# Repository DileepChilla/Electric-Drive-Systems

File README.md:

# 24 V / 250 W Brushed DC Motor Driver

**IR2104 half-bridge · 2× IRFZ44N · ATmega328P closed-loop control**

Design, simulation, PCB layout, firmware and bench validation of a complete motor
drive for a MY1016 24 V 250 W brushed DC motor. Built for ELT10140 *Electric Drive
Systems*, Westsächsische Hochschule Zwickau, summer semester 2026.

---

## What this is

A single-quadrant (unidirectional) drive with hardware and software overcurrent
protection, soft-start, stall detection and a five-state supervisory state machine.
The design was carried through the full V-cycle: analytical sizing → SPICE/VSM
co-simulation → averaged-model verification in Simulink → PCB layout → assembly →
bench test.

| Metric | Value |
|---|---|
| Supply | 24 V DC, 15 A fused |
| Rated output | 250 W |
| Switching frequency | 20 kHz (Timer1 Fast PWM, ICR1 top) |
| Duty resolution | 10 bit (ICR1 = 799 @ 16 MHz, /1 prescaler) |
| Current sense | 10 mΩ shunt, ×16 non-inverting, 0–31 A → 0–5 V |
| Overcurrent trip | Hardware SD assert + firmware stall detect (> 20 A for > 1 s) |
| Board | 2-layer FR-4, 1.55 mm, 35 µm Cu |

---

## Architecture

```
24 V ──┬── LM2596 buck ──── 5 V ──── ATmega328P (Arduino Nano)
       │                                  │ OC1A (D9) ──► IN
       ├── L7812CV linear ── 12 V ────► IR2104 ──┬──► HO ──► Q1 (IRFZ44N, high side)
       │                                  ▲      └──► LO ──► Q2 (IRFZ44N, low side)
       │                            SD ───┘
       │                          (D8 + hardware fault)
       │
       └── power rail ──► Q1 drain
                          switch node ──► MY1016 motor ──► MBR2045CT ──► shunt ──► GND
                                                                          │
                                                          LM358 ×16 ──► ADC0 (A0)
```

### Design decisions worth defending

**IR2104 VCC must be 12 V, not 24 V and not 5 V.**
The device UVLO sits at ~8.2 V rising, so 5 V logic rails cannot drive it; 24 V exceeds
its absolute maximum. A dedicated L7812CV linear regulator supplies VCC. This is the
single most common way to destroy an IR2104 and the reason the design carries a second
regulator despite the buck already producing 5 V.

**Bootstrap sizing.**
1 µF ceramic + 1N4148 fast diode. At 20 kHz the high-side gate charge (Q_g ≈ 63 nC for
IRFZ44N) is replenished every 50 µs; the capacitor must hold V_BS above the 8.0 V
bootstrap UVLO across the maximum on-time. Minimum duty is clamped in firmware so the
low-side device always conducts long enough to recharge.

**Synchronous rectification over a plain flyback diode.**
Q2's channel resistance (17.5 mΩ) dissipates less than the forward drop of the Schottky
during freewheeling. The MBR2045CT remains as a parallel path covering the dead time
and as a fail-safe if the low-side gate drive is lost.

**20 kHz PWM.**
Above the audible band, below the point where IRFZ44N switching losses become the
dominant thermal term (≈ 0.35 W per device at rated current with 10 Ω gate resistors).

**Two independent overcurrent layers.**
Hardware pulls SD low in sub-microsecond time — fast enough for a short circuit.
Firmware stall detection acts on the filtered ADC current over a 1 s window — slow, but
it distinguishes a genuine mechanical jam from inrush. Neither alone is sufficient.

---

## Repository layout

```
├── firmware/          Arduino/AVR source — PWM, ADC, state machine, protection
├── hardware/
│   ├── kicad/         KiCad 10 project: schematic, PCB, footprints
│   ├── gerbers/       Fabrication output + drill files
│   └── datasheets/    Component datasheets referenced in the design
├── simulation/
│   ├── proteus/       Proteus VSM mixed-signal co-simulation (.pdsprj)
│   ├── simulink/      Averaged-model plant + discrete state machine (.slx)
│   └── results/       Captured waveforms, step responses, fault traces
├── design/            Engineering notes and derivations
├── report/            Final report (PDF) and presentation
├── bom/               Bill of materials (CSV + PDF)
└── images/            Diagrams, board photos, schematic exports
```

---

## Firmware

Bare-register AVR C++, no Arduino `analogWrite`. Timer1 in Fast PWM mode 14
(TOP = ICR1) gives a fixed 20 kHz carrier with 10-bit duty resolution.

State machine:

```
OFF ──start──► STARTING ──ramp complete──► RUNNING
 ▲                 │                          │
 │                 └──────overcurrent─────────┤
 │                                            │
 └── BRAKING ◄── stop ──────────────────────► FAULT
```

- `STARTING` ramps duty linearly to limit inrush through the motor's armature inductance.
- `FAULT` latches: SD is driven low and the state persists until an explicit reset.
- `BRAKING` shorts the armature through Q2 for dynamic braking.
- Current is read in a 4-sample exponential moving average to reject switching noise
  without adding the phase lag of a long boxcar filter.

Build: Arduino IDE or PlatformIO, target `nanoatmega328new`, 16 MHz.

---

## Simulation

**Proteus VSM** — the only tool in the chain that runs the compiled firmware against a
SPICE model of the analog stage simultaneously. Used to verify gate drive timing,
bootstrap charging, and that the ADC path actually produces the expected count for a
known shunt current.

> Note: Proteus *Analogue Analysis* is pure SPICE and does not execute the MCU
> firmware. Mixed-signal capture requires the VSM Oscilloscope instrument.
> AREF (ATmega328P pin 20) must be tied to +5 V or every ADC read returns zero and the
> overcurrent path silently fails.

**Simulink** — `MotorDriverAveraged.slx` replaces the switching stage with a duty-cycle
averaged model, letting the electrical (R–L–back-EMF) and mechanical (J–B–T_load)
dynamics run at reasonable step sizes. The firmware state machine is reimplemented in a
discrete MATLAB Function block, together with 10-bit ADC quantisation and the LM358
scaling, so the simulated controller sees the same numbers the real one does.

Two validated scenarios: light-load run-and-brake, and a rotor jam triggering the fault
path.

*Known limitation:* the load-torque model is constant rather than velocity-dependent, so
after a fault the plant shows a small reverse rotation that the real machine does not.
Documented rather than hidden — fixing it requires a Coulomb-friction/zero-speed
constraint on the mechanical block.

---

## Bill of materials

Full BOM in `bom/`. Principal parts:

| Ref | Part | Function |
|---|---|---|
| M1 | MY1016 | 24 V 250 W brushed DC motor |
| U1 | IR2104 | Half-bridge gate driver, bootstrap high-side |
| Q1, Q2 | IRFZ44N | 55 V / 49 A N-channel MOSFET, R_DS(on) 17.5 mΩ |
| D2 | MBR2045CT | 20 A Schottky freewheeling diode |
| U2 | LM358 | Current-sense amplifier, gain 16 |
| U4 | LM2596 module | 24 V → 5 V switching regulator |
| U5 | L7812CV | 24 V → 12 V linear regulator (IR2104 VCC) |
| D1 | 1N4148 | Bootstrap diode |
| — | SMBJ33A | Transient voltage suppressor, input protection |
| R_sh | 10 mΩ, 3 W | Current-sense shunt |

Mechanical: 400 × 300 × 12 mm birch plywood mounting board, ferrule-crimped
connections throughout.

---

## Reproducing

1. Open `hardware/kicad/` in KiCad 10.0 or later.
2. Flash `firmware/` to an Arduino Nano (ATmega328P, 16 MHz).
3. Supply 24 V through a 15 A fuse. **Confirm the L7812CV output is 12 V before
   connecting IR2104 VCC.**
4. Verify the switch node with an isolated probe before attaching the motor.

---

## Course context

ELT10140 Electric Drive Systems, SoSe 2026 · Westsächsische Hochschule Zwickau
Supervisors: Prof. Dr.-Ing. J. Zitzelsberger, Prof. U. David, Prof. R. Lehmann
Team 1 — Leo Kämpf (team lead), Dileep Chilla (documentation, simulation, PCB),
Vaibhav, Rahul, Shashank, Usman, Vaishali, Laert

Course handouts and lecture material are the property of WHZ and are not redistributed
in this repository.

## Licence

Source code and design files: MIT (see `LICENSE`).
Documentation and figures: CC BY 4.0.

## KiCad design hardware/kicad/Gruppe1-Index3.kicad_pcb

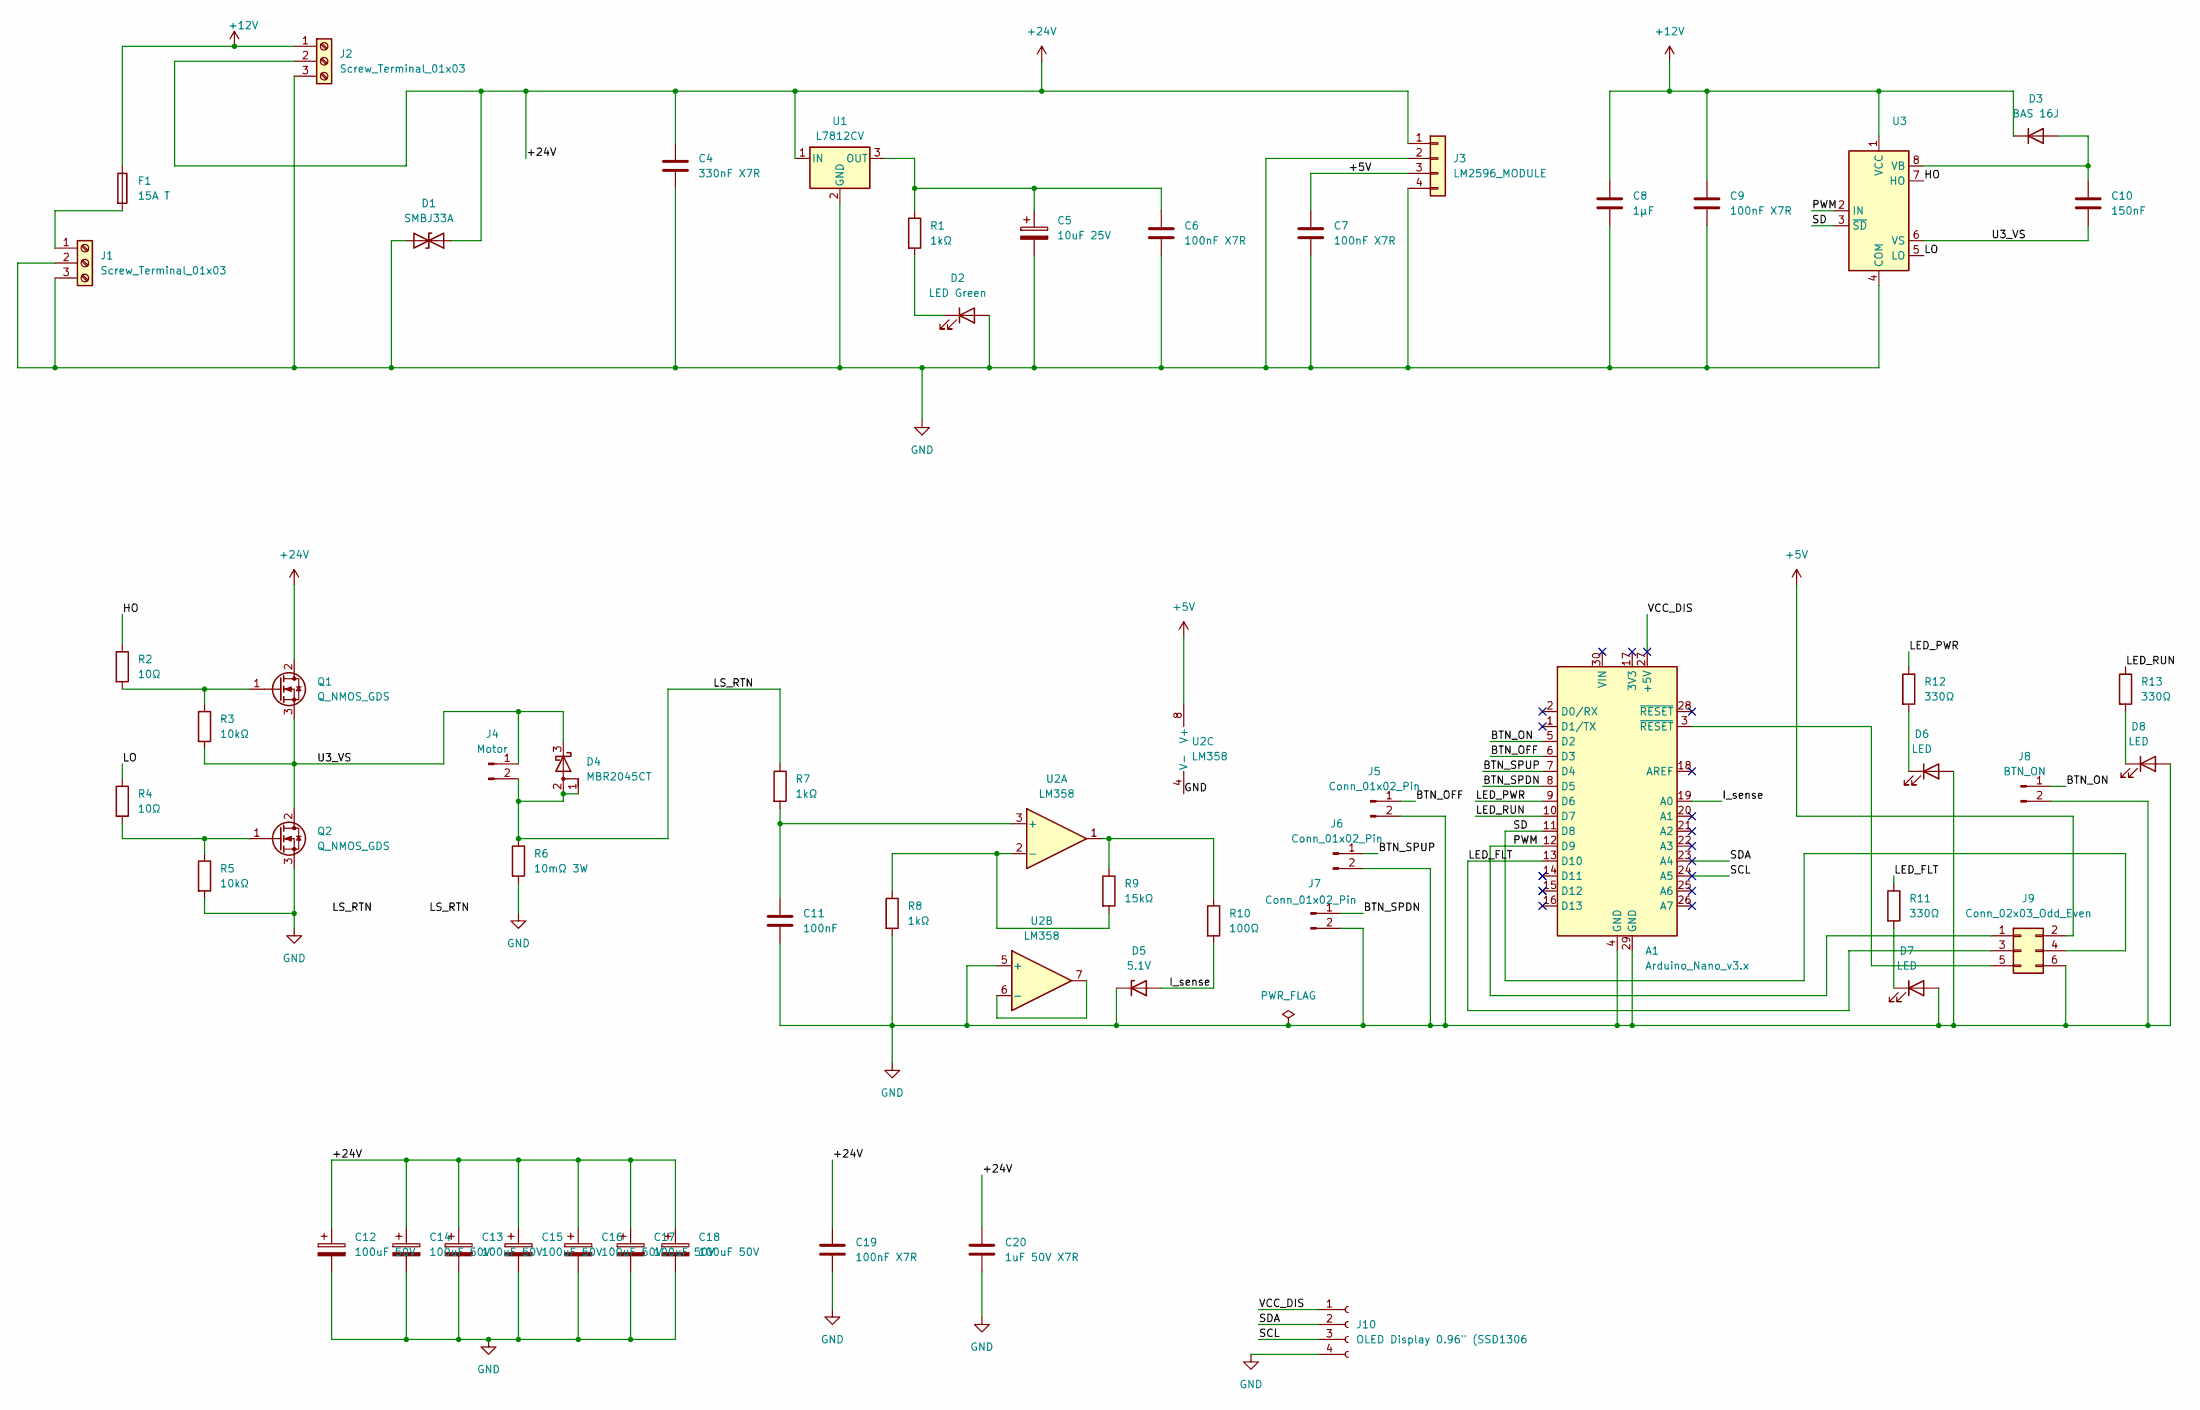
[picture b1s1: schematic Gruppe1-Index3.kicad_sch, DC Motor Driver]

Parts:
A1: Arduino_Nano_v3.x; Arduino_Nano
C4: 330nF X7R; C_1206_3216Metric
C5: 10uF 25V; C_1206_3216Metric
C6, C7, C9, C19: 100nF X7R; C_1206_3216Metric
C8: 1µF; C_1206_3216Metric
C10: 150nF; C_1206_3216Metric
C11: 100nF; C_1206_3216Metric
C12, C13, C14, C15, C16, C17, C18: 100uF 50V; CP_Elec_10x10.5
C20: 1uF 50V X7R; C_1206_3216Metric
D1: SMBJ33A; D_SMA-SMB_Universal_Handsoldering
D2: LED Green; LED_1206_3216Metric_Pad1.42x1.75mm_HandSolder
D3: BAS 16J; D_SOD-323F
D4: MBR2045CT; TO-263-3_TabPin2
D5: 5.1V; D_MiniMELF_Handsoldering
D6, D7, D8: LED; LED_1206_3216Metric_Pad1.42x1.75mm_HandSolder
F1: 15A T; Fuseholder_Cylinder-5x20mm_Stelvio-Kontek_PTF78_Horizontal_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
J1, J2: Screw_Terminal_01x03; TerminalBlock_Phoenix_PT-1,5-3-5.0-H_1x03_P5.00mm_Horizontal
J3: LM2596_MODULE; PinHeader_1x04_P2.54mm_Vertical
J4: Motor; TerminalBlock_Phoenix_MKDS-1,5-2-5.08_1x02_P5.08mm_Horizont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
J5, J6, J7: Conn_01x02_Pin; PinHeader_1x02_P2.54mm_Vertical
J8: BTN_ON; PinHeader_1x02_P2.54mm_Vertical
J9: Conn_02x03_Odd_Even; PinHeader_2x03_P2.54mm_Vertical
J10: OLED Display 0.96" (SSD1306; PinHeader_1x04_P2.54mm_Vertical
Q1, Q2: Q_NMOS_GDS; TO-263-3_TabPin2
R1, R7, R8: 1kΩ; R_0603_1608Metric_Pad0.98x0.95mm_HandSolder
R2, R4: 10Ω; R_0805_2012Metric_Pad1.20x1.40mm_HandSolder
R3, R5: 10kΩ; R_1206_3216Metric_Pad1.30x1.75mm_HandSolder
R6: 10mΩ 3W; R_Axial_Power_L20.0mm_W6.4mm_P25.40mm
R9: 15kΩ; R_1206_3216Metric_Pad1.30x1.75mm_HandSolder
R10: 100Ω; R_1206_3216Metric_Pad1.30x1.75mm_HandSolder
R11, R12, R13: 330Ω; R_1206_3216Metric_Pad1.30x1.75mm_HandSolder
U1: L7812CV; TO-220-3_Vertical
U2: LM358; DIP-8_W7.62mm
U3: IR2104; DIP-8_W7.62mm

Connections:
+5V: C7.1, J3.3, J9.2, U2.8 (V+)
+12V: C8.1, C9.1, D3.1 (K), F1.1, J2.1, U3.1 (VCC)
+24V: C4.1, C12.1, C13.1, C14.1, C15.1, C16.1, C17.1, C18.1, C19.1, C20.1, D1.1 (A1), J2.2, J3.1, Q1.2 (D), U1.1 (IN)
/BTN_OFF: A1.6 (D3), J5.1
/BTN_ON: A1.5 (D2), J8.1
/BTN_SPDN: A1.8 (D5), J7.1
/BTN_SPUP: A1.7 (D4), J6.1
/HO: R2.1, U3.7 (HO)
/I_sense: A1.19 (A0), D5.2 (A), R10.2
/LED_FLT: A1.13 (D10), J9.3, R11.1
/LED_PWR: A1.9 (D6), R12.1
/LED_RUN: A1.10 (D7), R13.1
/LO: R4.1, U3.5 (LO)
/LS_RTN: D4.1 (A), D4.2 (A), J4.2, R6.1, R7.1
/PWM: A1.12 (D9), J9.1, U3.2 (IN)
/SCL: A1.24 (A5), J10.3
/SD: A1.11 (D8), J9.4, U3.3 (~SD)
/SDA: A1.23 (A4), J10.2
/U3_VS: C10.2, D4.3 (K), J4.1, Q1.3 (S), Q2.2 (D), R3.2, U3.6 (VS)
/VCC_DIS: A1.27 (+5V), J10.1
GND: A1.4 (GND), A1.29 (GND), C4.2, C5.2, C6.2, C7.2, C8.2, C9.2, C11.2, C12.2, C13.2, C14.2, C15.2, C16.2, C17.2, C18.2, C19.2, C20.2, D1.2 (A2), D2.2 (A), D5.1 (K), D6.2 (A), D7.2 (A), D8.2 (A), J1.2, J1.3, J2.3, J3.2, J3.4, J5.2, J6.2, J7.2, J8.2, J9.6, J10.4, Q2.3 (S), R5.2, R6.2, R8.2, U1.2 (GND), U2.4 (V-), U2.5 (+), U3.4 (COM)
unnamed: D2.1 (K), R1.2
unnamed: C10.1, D3.2 (A), U3.8 (VB)
unnamed: D6.1 (K), R12.2
unnamed: D7.1 (K), R11.2
unnamed: D8.1 (K), R13.2
unnamed: F1.2, J1.1
unnamed: A1.3 (~RESET), J9.5
unnamed: Q1.1 (G), R2.2, R3.1
unnamed: Q2.1 (G), R4.2, R5.1
unnamed: R9.1, R10.1, U2.1
unnamed: C5.1, C6.1, R1.1, U1.3 (OUT)
unnamed: C11.1, R7.2, U2.3 (+)
unnamed: R8.1, R9.2, U2.2 (-)
unnamed: U2.6 (-), U2.7

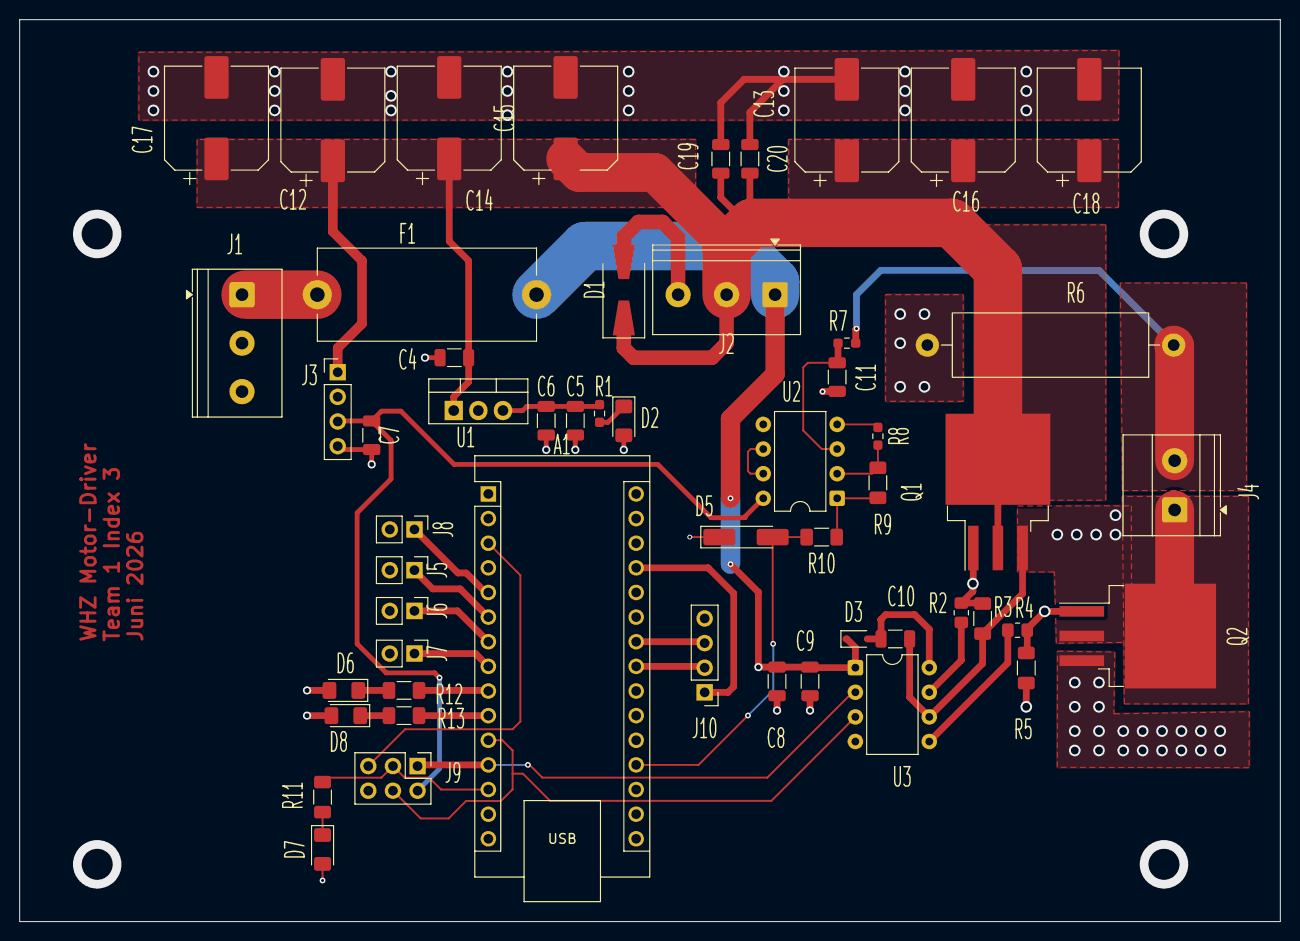
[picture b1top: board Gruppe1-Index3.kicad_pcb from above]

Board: 2 copper layers, 130.0 x 93.0 mm, 55 parts (1 on the bottom side), 35 nets.

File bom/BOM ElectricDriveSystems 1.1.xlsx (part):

Team 1
24V / 250W Brushed DC Motor Driver IR2104 Half-Bridge
Includes: PCB components, connection materials, mechanical hardware and motor
# | Reference | Qty | Value / Description | Spec | Source | Unit € (est.) | Total € | Notes
A — PCB ELECTRONIC COMPONENTS (from KiCad BOM)
A.1 — Power Stage
1 | Q1, Q2 | 2 | IRFZ44NSPBF MOSFET N-Ch | D²Pak, 55V 49A 0,0175Ω | https://www.reichelt.de/de/de/shop/produkt/mosfet_n-ch_55v_4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 | 0.91 | 1.82 | Half-bridge switches
2 | D4 | 1 | MBRS2045CT Schottky diode | D²Pak, 20A 45V | https://www.reichelt.de/de/de/shop/produkt/smd-schottky_45v_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 | 0.9 | 0.9 | Freewheeling — CORRECTED from 1N5822
3 | F1 | 1 | LITT 0287015 | Littlefuse KFZ-Sicherung, ATO, 15 A, blau | https://www.reichelt.de/de/de/shop/produkt/kfz-sicherung_ato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 | 0.87 | 0.87 | Input protection
4 | D1 | 1 | P4SMAJ33CA | TVS-Diode, bidirektional, 33 V, 400 W, DO-214AC/SMA | https://www.reichelt.de/de/de/shop/produkt/tvs-diode_bidirek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 | 0.1 | 0.1 | 24V transient clamp
5 | D3 | 2 | BAS 16J | SMD Si all-purpose diodes, SOD323F, 100 V, 0.25 A | https://www.reichelt.com/ie/en/shop/product/smd_si_all-purpo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 | 0.03 | 0.06 | Bootstrap diode
6 | D5 | 1 | nexperia BZV 55-C5V1 NXP | Zenerdiode, 5,1 V, 0,5 W, SOD-80 | https://www.reichelt.de/de/de/shop/produkt/zenerdiode_5_1_v_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 | 0.02 | 0.02 | Voltage reference/protection
46143 |  | 2 | fischer Elektronik FK 244 13 D2 PAK | Kühlkörper, 13 mm, Kupfer, 22,8 K/W, PowerSO-10/SO-14/SO-16/SO-8 | https://www.reichelt.de/de/de/shop/produkt/kuehlkoerper_13_m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 | 0.99 | 1.98 | Kühlkörper für D2Pak Mosfets
A.2 — Voltage Regulation
7 | U1 | 1 | L7812CV STM 12V linear regulator | TO-220 | https://www.reichelt.de/de/de/shop/produkt/spannungsregler_f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 | 0.23 | 0.23 | Mandatory: IR2104 VCC (UVLO 8.2V)
8 | J3 | 1 | LM2596S DEBO DCDC 2.5W | Entwicklerboards - Spannungsregler 2,5 W, DC/DC-Wandler, LM2596S, 4-pin header 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 | https://www.reichelt.de/de/de/shop/produkt/entwicklerboards_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 | 2.99 | 2.99 | 24V → 5V for Arduino
A.3 — Control & Driver
9 | A1 | 1 | Arduino Nano v3.x (ATmega328P) | Module, 16 MHz, 5V |  |  | 0 | Main controller
10 | U3 | 1 | IR2104 half-bridge gate driver | DIP-8 | https://www.reichelt.de/de/de/shop/produkt/brueckentreiber_h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 | 1.3 | 1.3 | 520ns deadtime, SD pin
11 | U2 | 1 | LM 358 DIP dual op-amp | DIP-8 | https://www.reichelt.de/de/de/shop/produkt/operationsverstae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 | 0.25 | 0.25 | Current sense amplifier (G≈16)
A.4 — Capacitors
12 | C1 | 8 | ELKO-Polymere Hybrid SMD, 100 µF, 50 V, 145°C | 10,0 x 10,2 mm | https://www.reichelt.de/de/de/shop/produkt/elko-polymere_hyb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 | 1.7 | 13.6 | Input bulk decoupling, eliminating ripple current
14 | C3, C6, C7,C9,C11 | 10 | Wasin 1206B104K500CT | SMD-Kerko, 1206, 100 nF, 50V, 10%, X7R, MLCC | https://www.reichelt.de/de/de/shop/produkt/smd-kerko_1206_10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 | 7.0000000000000007E-2 | 0.70000000000000007 | IC decoupling
15 | C4 | 5 | Wasin WAL 1206B334K500 | SMD-Kerko, 1206, 330 nF, 50V, 10%, X7R, MLCC | https://www.reichelt.de/de/de/shop/produkt/smd-kerko_1206_33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 | 7.0000000000000007E-2 | 0.35000000000000003
16 | C5 | 10 | Samsung CL31B106KBHNNNE | MLCC, 1206, 10uF, 50V, X7R, ±10%, H1,6 mm | https://www.reichelt.de/de/de/shop/produkt/mlcc_1206_10uf_50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 | 0.46 | 4.6000000000000005
17 | C2, C8, C10 | 10 | muRata GRM31CR72A105K | MLCC, 1206, 1µF, 100 V, ±10%, X7R | https://www.reichelt.de/de/de/shop/produkt/mlcc_1206_1_f_100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 | 0.14000000000000001 | 1.4000000000000001 | Bootstrap capacitors
A.5 — Resistors
20 | R1, R7, R8 | 3 | RND 0603 1 93,1K | SMD-Widerstand, 0603, 93,1 kOhm, 100 mW, 1% | https://www.reichelt.de/de/de/shop/produkt/smd-widerstand_06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 | 0.02 | 0.06 | Pull-up / general
21 | R2, R4 | 2 | RND 1550805 AH | SMD-Widerstand, 0805, 10 Ohm, 125 mW, 5% | https://www.reichelt.de/de/de/shop/produkt/smd-widerstand_08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 | 0.02 | 0.04 | Gate resistors (di/dt limit)
22 | R3, R5 | 2 | Wasin WAL WR12X1002FTL | SMD-Widerstand, 1206, 10 kOhm, 250 mW, 1% | https://www.reichelt.de/de/de/shop/produkt/smd-widerstand_12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 | 0.02 | 0.04 | Gate pull-downs
23 | R6 | 1 | VIT KN350-85B0R1 | VIT KN350-85B0R1 | https://www.reichelt.de/de/de/shop/produkt/drahtwiderstand_a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 | 0.75 | 0.75 | Current sense shunt
24 | R9 | 1 | Waisin WAL WR12X1502FTL | SMD-Widerstand, 1206, 15 kOhm, 250 mW, 1% | https://www.reichelt.de/de/de/shop/produkt/smd-widerstand_12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 | 0.02 | 0.02 | Op-amp gain (1k+15k=G16)
25 | R10 | 1 | Vishay VIS CRCW12061002 | SMD-Widerstand, 1206, 100 Ohm, 250 mW, 1% | https://www.reichelt.de/de/de/shop/produkt/smd-widerstand_12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 | 0.09 | 0.09 | LED current limit
26 | R11, R12, R13 | 3 | Wasin WR12X3300FTL | SMD-Widerstand, 1206, 330 Ohm, 250 mW, 1% | https://www.reichelt.de/de/de/shop/produkt/smd-widerstand_12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 | 0.02 | 0.06 | Status LED resistors
A.6 — LEDs & Indicators
27 | D2 | 2 | Everlight EVL 11-21SYGC | SMD-LED 1206, Super-Gelb-Grün, AlGaInP, 29 mcd, 60°, 3,0 x 1,5mm | https://www.reichelt.de/de/de/shop/produkt/smd-led_1206_supe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 | 0.05 | 0.1 | Power-on indicator
 |  | 1 | EVL 11-21SURC/S2 | LED, SMD 1206, rot, 180 mcd, 60° | https://www.reichelt.de/de/de/shop/produkt/led_smd_1206_rot_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 | 7.0000000000000007E-2
28 | D6, D7, D8 | 1 | Huiyuan 1206Y1C-KHA-C | LED, SMD 1206, gelb, 150 mcd, 120° | https://www.reichelt.de/de/de/shop/produkt/led_smd_1206_gelb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 | 0.09 | 0.09 | Status: run / fault / PWM
A.7 — PCB Connectors
29 | J1 | 1 | 24V_IN screw terminal DG127 5,08-2 | Phoenix MKDS 1.5/2 P5mm | https://www.reichelt.de/de/de/shop/produkt/leiterplattenklem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 | 0.33 | 0.33 | 24V input
30 | J2 | 1 | MAIN_PWR screw terminal DG127 5,08-2 | Phoenix MKDS 1.5/2 P5mm | https://www.reichelt.de/de/de/shop/produkt/leiterplattenklem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 | 0.33 | 0.33 | Main power bus
31 | J4 | 1 | Motor output screw terminal DG127 5,08-2 | Phoenix MKDS 1.5/2 P5.08mm | https://www.reichelt.de/de/de/shop/produkt/leiterplattenklem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 | 0.33 | 0.33 | Motor M+/M−
32 | J5, J6, J7 | 3 | MPE 087-1-002 | PinHeader 1×02 P2.54mm | https://www.reichelt.de/de/de/shop/produkt/stiftleisten_2_54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 | 0.06 | 0.18 | Signal jumpers
33 | J8 | 1 | BTN_ON 2-pin header | PinHeader 1×02 P2.54mm | https://www.reichelt.de/de/de/shop/produkt/stiftleisten_2_54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 | 0.06 | 0.06 | ON button input
34 | J9 | 1 | ISP/button 2×3 header MPE 087-2-006 | PinHeader 2×03 P2.54mm | https://www.reichelt.de/de/de/shop/produkt/stiftleisten_2_54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 | 0.16 | 0.16 | Programming / button input
 |  | 2 | BKL Electronic BKL 10120953 | Buchsenleiste 2,54mm 1x16 gerade | https://www.reichelt.de/de/de/shop/produkt/buchsenleiste_2_5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 | 0.99 | 1.98 | Arduino Pinverbindung
35 | — | 1 | Fuse holder 5×20mm | Horizontal open mount | https://www.reichelt.de/de/de/shop/produkt/sicherungshalter_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 | 0.27 | 0.27 | For F1
SUBTOTAL A — PCB Components |  |  |  |  |  |  | 36.060000000000009 | ~50 individual components
B — CONNECTION MATERIALS (per Project Hints Appendix 5)
B.1 — Cables & Wires
36 | W1 | 1 | 12 AWG / 4mm² silicone wire RED (5m) | Stranded, 600V rated | https://www.amazon.de/QWORK%C2%AE-12AWG-Silikon-Elektronik-K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 | 11.99 | 11.99 | 24V power bus, motor+, ≥15A capable
37 | W2 | 1 | 12 AWG / 4mm² silicone wire BLACK (5m) | Stranded, 600V rated | https://www.amazon.de/QWORK%C2%AE-12AWG-Silikon-Elektronik-K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 | 11.99 | 11.99 | GND return, motor−
 |  | 1 | DEBO OLED2 0.96 | Entwicklerboards - Display, 0,96", OLED-Display, SSD1306 | https://www.reichelt.de/de/de/shop/produkt/entwicklerboards_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 | 6.99 | 6.99
38 | W3 | 1 | 22 AWG / 0.34mm² hookup wire set (6 colors) | 10m per color | https://www.amazon.de/Fermerry-Litzendraht-Kupferdrahtspule-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 | 14.89 | 14.89 | Signal: buttons, LEDs, I²C, ADC
39 | W4 | 1 | 18 AWG / 1mm² wire RED+BLACK (3m each) | Stranded | https://www.reichelt.de/de/de/shop/produkt/lautsprecherkabel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 | 3.1 | 3.1 | 12V/5V regulation bus
B.2 — Off-Board Connectors
40 | CON1 | 1 | XT60 panel-mount pair + pigtails | Male+Female, 60A rated | https://www.reichelt.de/de/de/shop/produkt/steckverbinder_fu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 | 2.99 | 2.99 | Battery / PSU input connector
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
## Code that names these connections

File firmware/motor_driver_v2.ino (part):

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#define SD_PIN        8    // IR2104 SD (HIGH = enabled, LOW = shutdown)
#define CURRENT_PIN   A0   // LM358 output → ATmega ADC0

#define BTN_ON        2    // ON button        (active LOW, INPUT_PULLUP)
#define BTN_OFF       3    // OFF button       (active LOW, INPUT_PULLUP)
#define BTN_SPEED_UP  4    // Speed Up button  (active LOW, INPUT_PULLUP)
#define BTN_SPEED_DN  5    // Speed Down button(active LOW, INPUT_PULLUP)
#define MAIN_SWITCH   10   // Latching switch  (active LOW, INPUT_PULLUP)

#define LED_RUN       6    // Green LED — motor running
#define LED_FAULT     7    // Red LED   — fault state

// ═══════════════════ CONSTANTS ═══════════════════
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void setup() {
    // Output pins
    pinMode(SD_PIN,   OUTPUT);
    pinMode(LED_RUN,  OUTPUT);
    pinMode(LED_FAULT, OUTPUT);
    digitalWrite(SD_PIN,    LOW);
    digitalWrite(LED_RUN,   LOW);
    digitalWrite(LED_FAULT, LOW);

    // Input pins (active LOW, internal pull-up)
    pinMode(BTN_ON,       INPUT_PULLUP);
    pinMode(BTN_OFF,      INPUT_PULLUP);
    pinMode(BTN_SPEED_UP, INPUT_PULLUP);
    pinMode(BTN_SPEED_DN, INPUT_PULLUP);
    pinMode(MAIN_SWITCH,  INPUT_PULLUP);
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
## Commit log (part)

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2026-04-06 Initial commit: ELT10140 Electric Drive Systems - 24V 250W DC Motor Driver
2026-04-06 Update block diagram: clean B&W redesign with all interfaces
2026-04-06 Remove milestone tracker, update supervisors
2026-04-06 Fix block diagram: high contrast B&W for GitHub dark mode
2026-04-06 Update block diagram
